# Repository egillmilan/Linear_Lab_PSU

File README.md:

# Linear Lab PSU
 Linear lab bench power supply project. The PCB consists of the rectification and the input filtering stage.

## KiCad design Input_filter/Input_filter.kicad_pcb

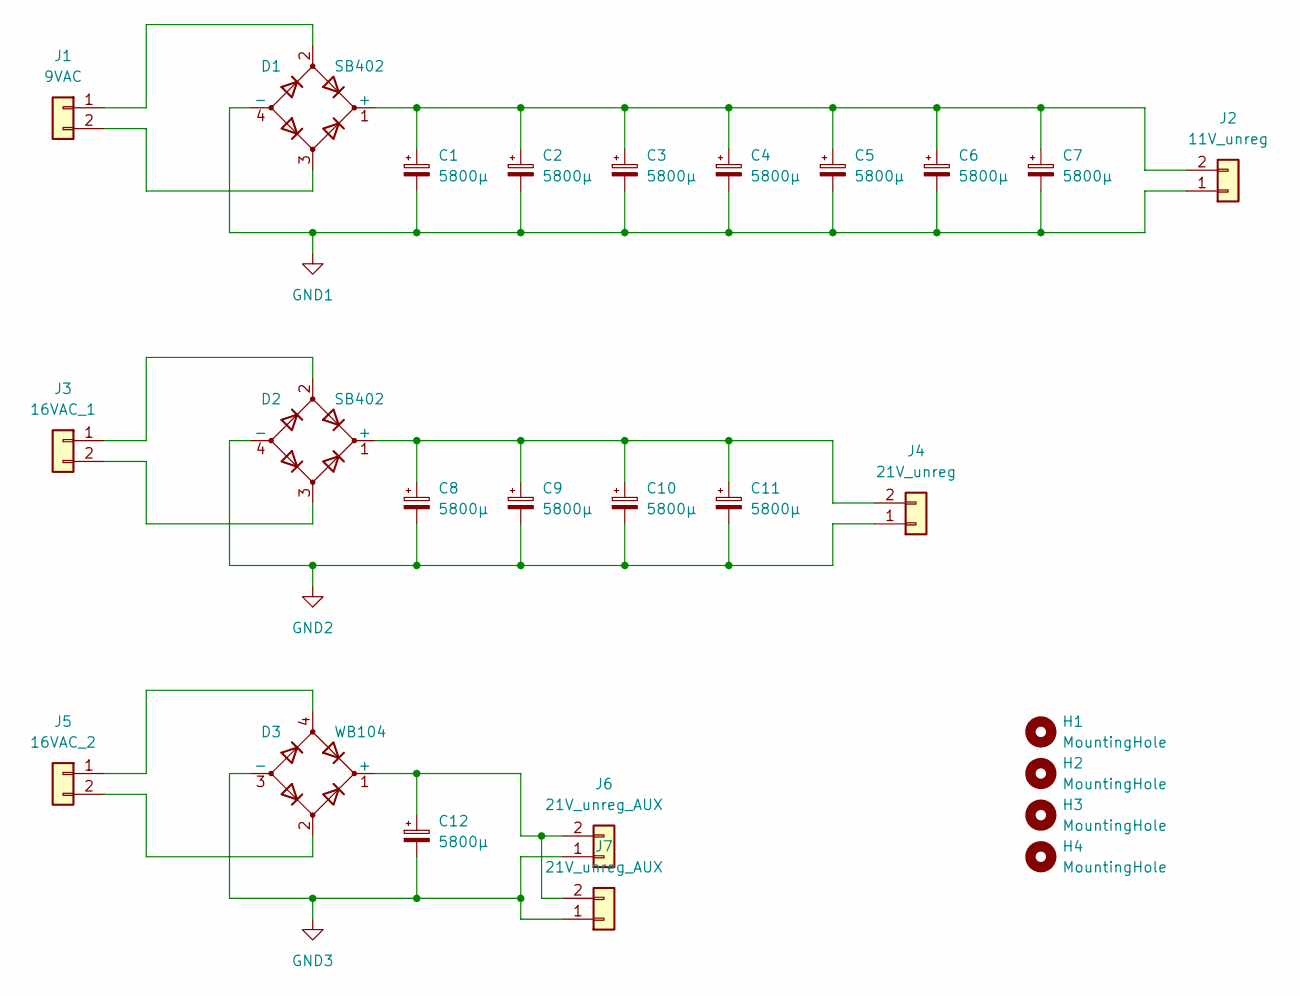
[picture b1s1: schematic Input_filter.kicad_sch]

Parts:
C1, C2, C3, C4, C5, C6, C7, C8, C9, C10, C11, C12: 5800µ; CP_Radial_D18.0mm_P7.50mm
D1, D2: SB402; Diode_Bridge_Vishay_KBL
D3: WB104; Diode_Bridge_Round_D9.0mm
H1, H2, H3, H4: MountingHole; MountingHole_3.2mm_M3
J1: 9VAC; TerminalBlock_Phoenix_MPT-0,5-2-2.54_1x02_P2.54mm_Horizontal
J2: 11V_unreg; TerminalBlock_Phoenix_MPT-0,5-2-2.54_1x02_P2.54mm_Horizontal
J3: 16VAC_1; TerminalBlock_Phoenix_MPT-0,5-2-2.54_1x02_P2.54mm_Horizontal
J4: 21V_unreg; TerminalBlock_Phoenix_MPT-0,5-2-2.54_1x02_P2.54mm_Horizontal
J5: 16VAC_2; TerminalBlock_Phoenix_MPT-0,5-2-2.54_1x02_P2.54mm_Horizontal
J6, J7: 21V_unreg_AUX; TerminalBlock_Phoenix_MPT-0,5-2-2.54_1x02_P2.54mm_Horizontal

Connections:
GND1: C1.2, C2.2, C3.2, C4.2, C5.2, C6.2, C7.2, D1.4 (-), J2.1
GND2: C8.2, C9.2, C10.2, C11.2, D2.4 (-), J4.1
GND3: C12.2, D3.3 (-), J6.1, J7.1
unnamed: C1.1, C2.1, C3.1, C4.1, C5.1, C6.1, C7.1, D1.1 (+), J2.2
unnamed: C8.1, C9.1, C10.1, C11.1, D2.1 (+), J4.2
unnamed: C12.1, D3.1 (+), J6.2, J7.2
unnamed: D1.2, J1.1
unnamed: D1.3, J1.2
unnamed: D2.2, J3.1
unnamed: D2.3, J3.2
unnamed: D3.2, J5.2
unnamed: D3.4, J5.1

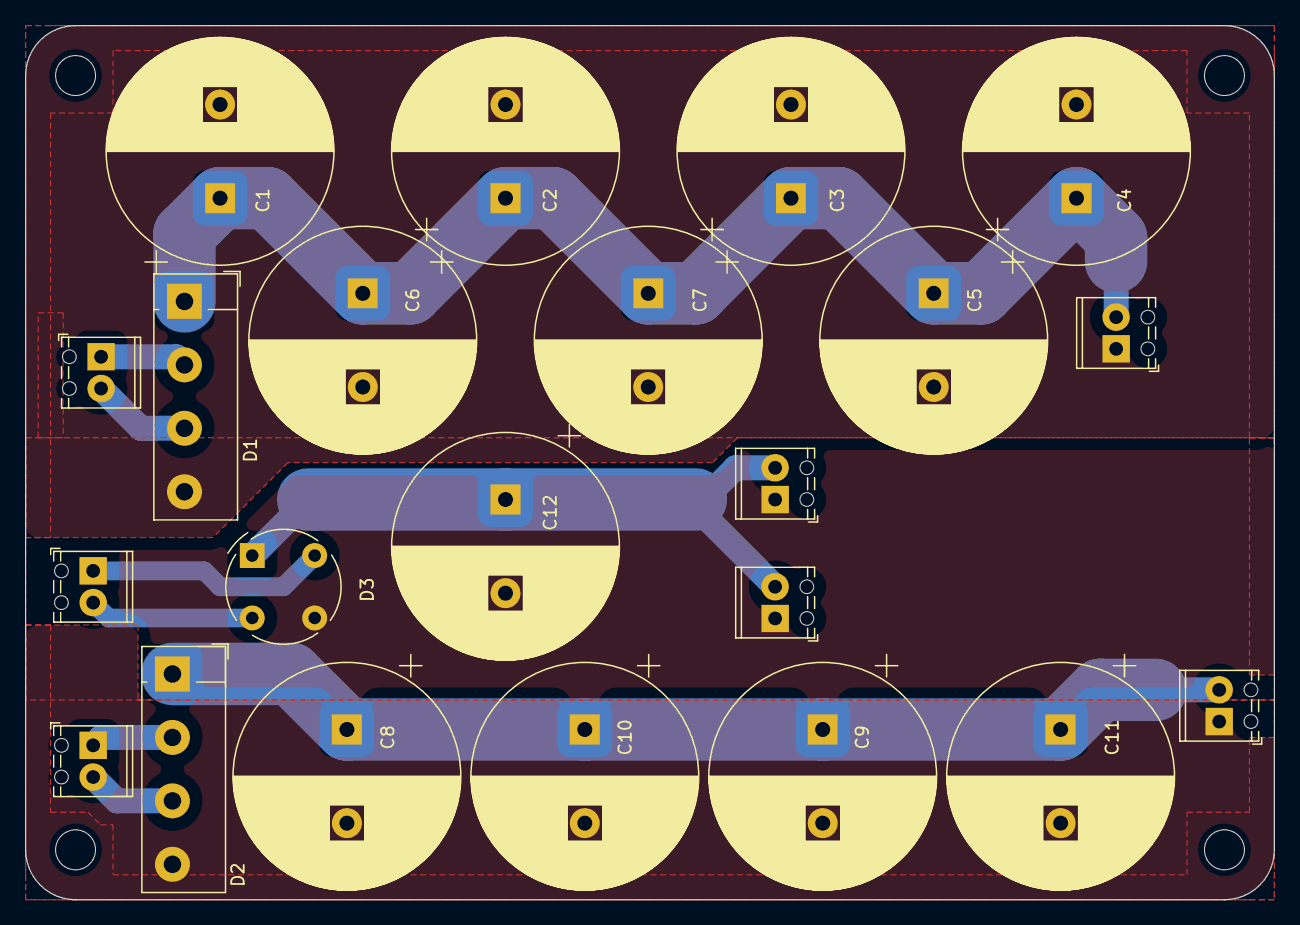
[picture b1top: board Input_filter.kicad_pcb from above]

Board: 2 copper layers, 100.0 x 70.0 mm, 26 parts (0 on the bottom side), 12 nets.

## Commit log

2023-04-18 Images
